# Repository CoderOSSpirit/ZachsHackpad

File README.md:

# ZachsHackpad
A macropad with four switches, a rotary encoder, and an OLED screen. It uses KMK firmware for operations. This macropad is designed to supplement traditional keyboards for gaming and work by streamlining certain common operations and making them easier for the user to execute.

# Features:
3D Printed Case with a seperate top and bottom cover
128x32 OLED display
4 programmable keys

# Cad Model:
The whole case fits together with 4 M3 bolts for the top and bottom of the case to attach to each other
Only 2 seperate printed pieces, with the printed circuit board fitting on the inside with all the parts
The top cover has room for all the parts

# PCB:

Included here is both the Schematic and PCB. Both the schematic and PCB were made in KiCad, with footprints from the OPL_KiCad_Library: https://github.com/Seeed-Studio/OPL_Kicad_Library/
Additional footprints were found a rotary encoder library: https://kicad.github.io/footprints/Rotary_Encoder and from a 0.91 inch OLED footprint found off of SnapMagic

Schematic: 

PCB:

# Firmware:
This macropad uses Arduino .ino files for firmware. I used Arduino IDE to flash the firmware onto the chip itself. Adafruit TinyUSB and HID libraries needed to be installed to properly flash firmware onto the chip. Firmware is still a work in progress. Currently, the keys are working, with updates to the OLED display and rotary encoder upcoming.

# Bill of Materials:

* Seeed XIAO RP2040
* 4 MX-Style switches
* 4 Blank DSA Keycaps
* 1 EC11 Rotary Encoder
* 1 0.91 inch OLED display with pin order GND-VCC-SCL-SDA
* 1 3D-printed case (two seperate parts)

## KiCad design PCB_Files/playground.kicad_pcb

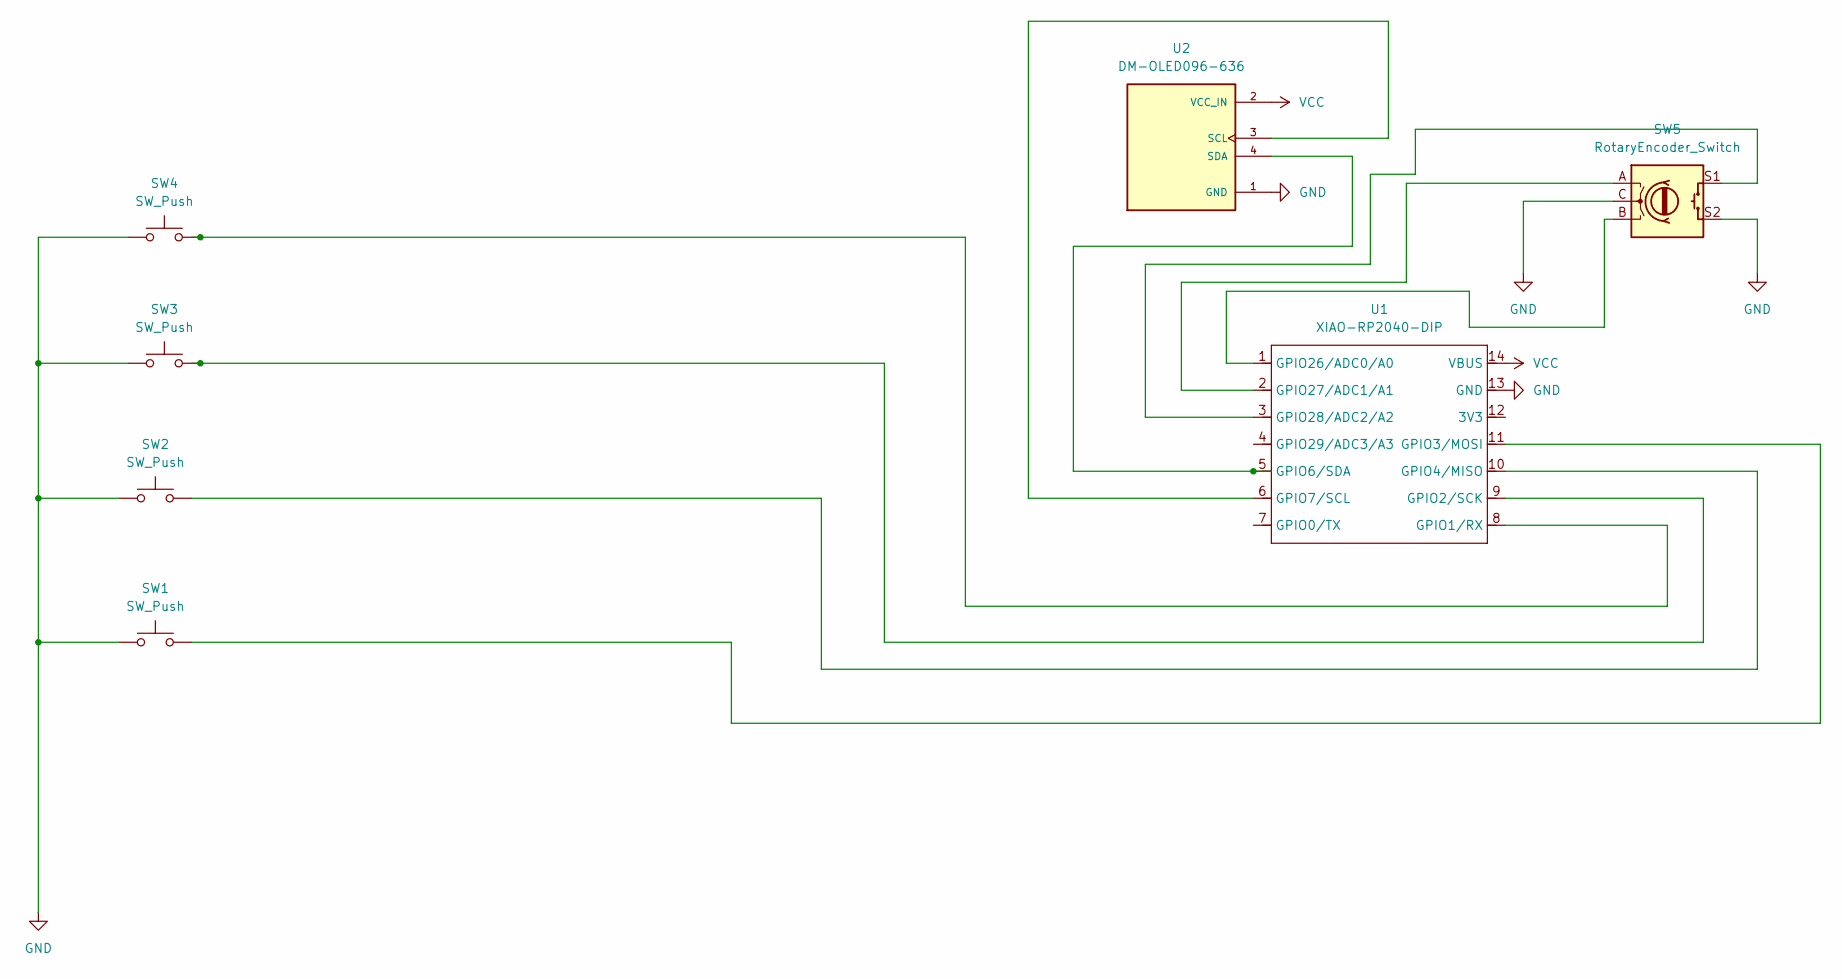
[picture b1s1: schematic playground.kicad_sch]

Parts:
SW1, SW2, SW3, SW4: SW_Push; SW_Cherry_MX_1.00u_PCB
SW5: RotaryEncoder_Switch; RotaryEncoder_Alps_EC11E-Switch_Vertical_H20mm
U1: XIAO-RP2040-DIP
U2: DM-OLED096-636; SSD1306-0.91-OLED-4pin-128x32; PARTREV 2018-09-10

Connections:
GND: SW1.1, SW2.1, SW3.1, SW4.1, SW5.C, SW5.S2, U1.13 (GND), U2.1 (GND)
unnamed: SW4.2, U1.8 (GPIO1/RX)
unnamed: SW3.2, U1.9 (GPIO2/SCK)
unnamed: SW1.2, U1.11 (GPIO3/MOSI)
unnamed: SW2.2, U1.10 (GPIO4/MISO)
unnamed: U1.5 (GPIO6/SDA), U2.4 (SDA)
unnamed: U1.6 (GPIO7/SCL), U2.3 (SCL)
unnamed: SW5.B, U1.1 (GPIO26/ADC0/A0)
unnamed: SW5.A, U1.2 (GPIO27/ADC1/A1)
unnamed: SW5.S1, U1.3 (GPIO28/ADC2/A2)
VCC: U1.14 (VBUS), U2.2 (VCC_IN)

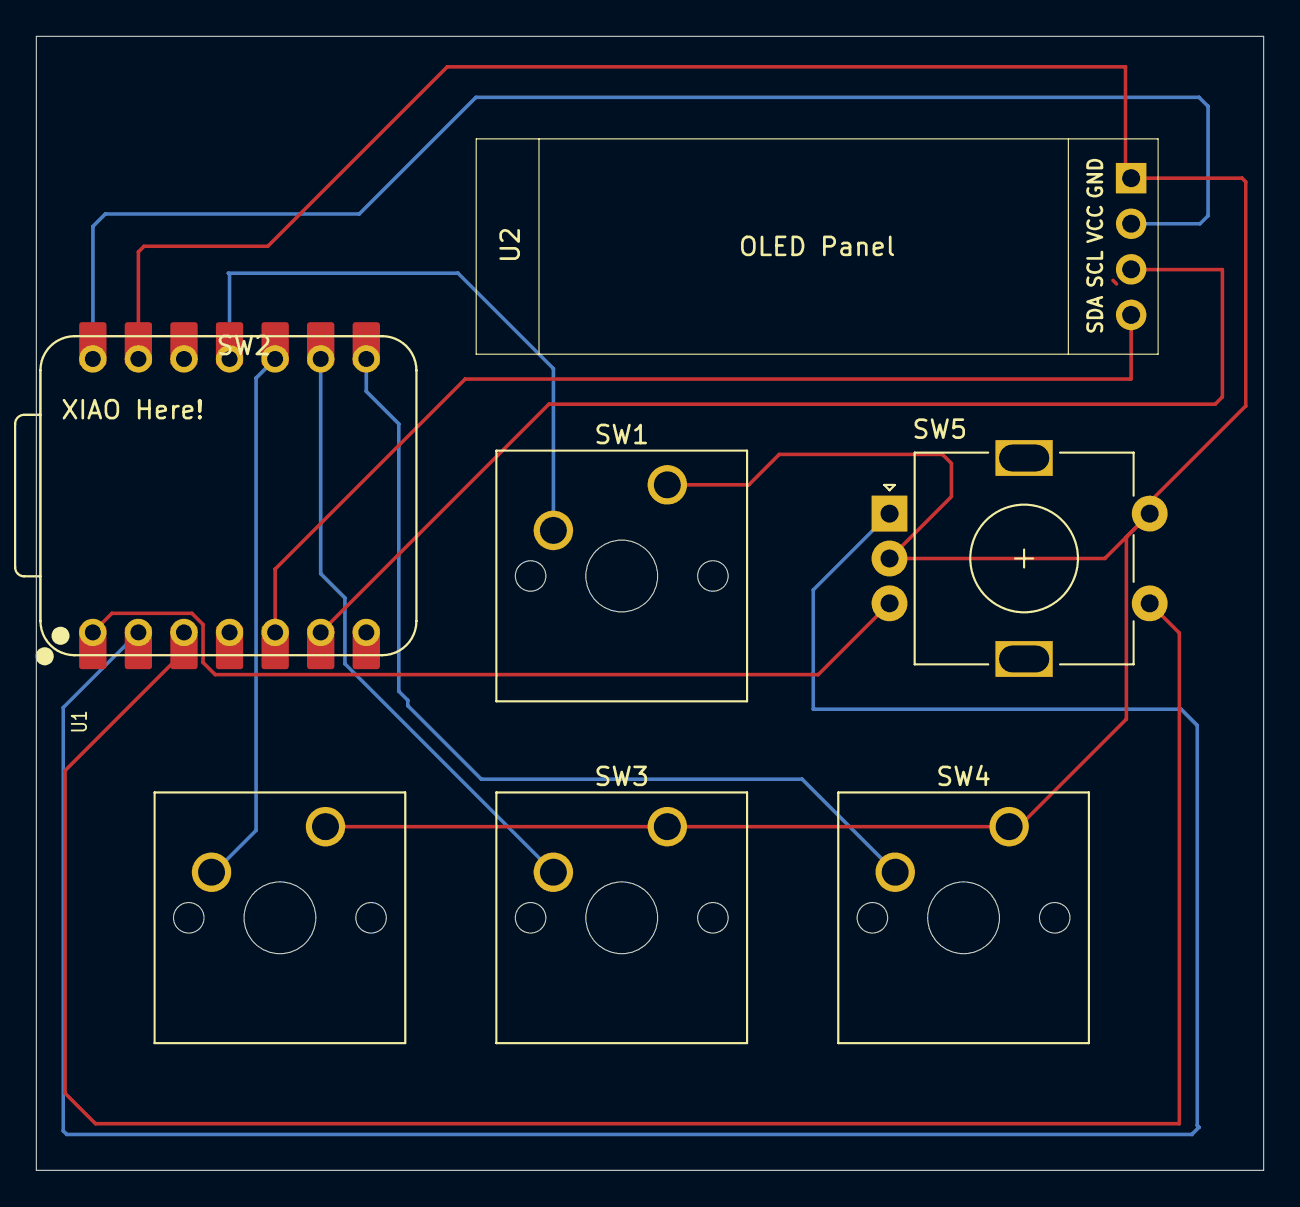
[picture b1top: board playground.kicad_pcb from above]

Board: 2 copper layers, 68.4 x 63.2 mm, 7 parts (0 on the bottom side), 11 nets.
